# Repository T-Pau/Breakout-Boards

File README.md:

# Connector Breakout Boards

### Easy Access to Pins of Common Connectors for Prototyping or Testing

## What Are These Boards?

They provide easy access to each pin of a connector via a pin header, labeled with the pin number and its use. If a connector contains multiple ground pins, these can be connected on the board via jumpers.

## Why Use These Boards?

They make testing or prototyping cables easier by providing a robust connection and avoiding mixing up pins.

## Getting Started

You can produce these boards

## D-Sub 9, 15, and 25

These connectors saw a wide variety of uses, therefore only pin numbers are provided on the silk screen. Each breakout board contains a pins and a socket connector.

### D-Sub 9 Bill of Materials

Amount | Part 
-------|-----
1      | 90° D-Sub-9 pins
1      | 90° D-Sub-9 socket
1      | 2x5 pin header

### D-Sub 15 Bill of Materials

Amount | Part 
-------|-----
1      | 90° D-Sub-15 pins
1      | 90° D-Sub-15 socket
1      | 2x8 pin header

### D-Sub 25 Bill of Materials

Amount | Part 
-------|-----
1      | 90° D-Sub-25 plug
1      | 90° D-Sub-25 socket
1      | 2x13 pin header

## VGA Breakout Board

This board exposes each pin of a VGA connector on a pin header. It also allows connecting each of the GND pins via jumpers.

### Bill of Materials

Amount | Part 
-------|-----
1      | 90° D-Sub-15 HD socket
1      | 2x4 pin header
1      | 2x8 pin header
4      | jumper

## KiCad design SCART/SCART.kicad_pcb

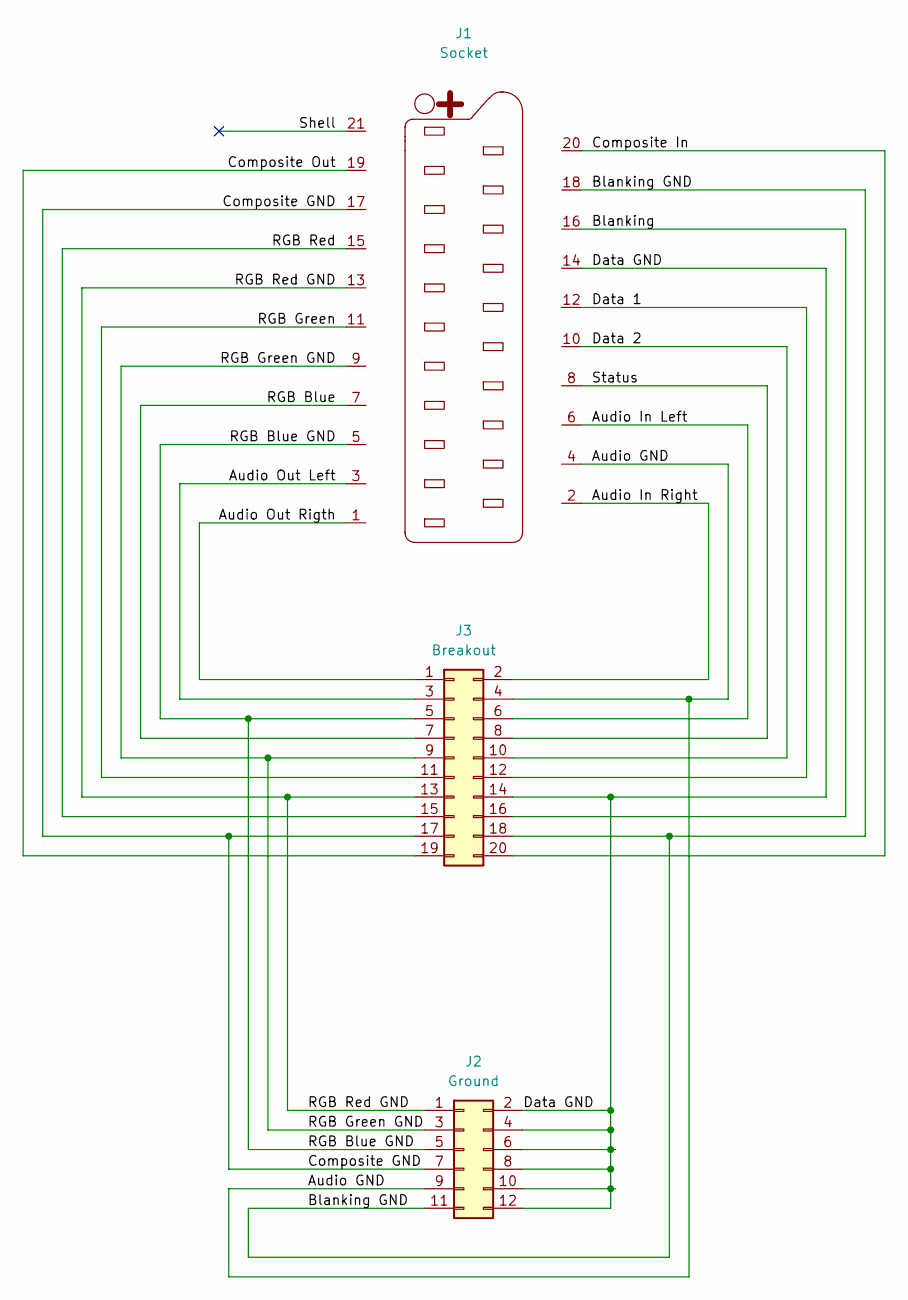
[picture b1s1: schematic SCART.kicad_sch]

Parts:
J1: Socket; SCART
J2: Ground; PinSocket_2x06_P2.54mm_Vertical
J3: Breakout; PinSocket_2x10_P2.54mm_Vertical

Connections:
/Audio GND: J1.4, J2.9, J3.4
/Audio In Left: J1.6, J3.6
/Audio In Right: J1.2, J3.2
/Audio Out Left: J1.3, J3.3
/Audio Out Rigth: J1.1, J3.1
/Blanking: J1.16, J3.16
/Blanking GND: J1.18, J2.11, J3.18
/Composite GND: J1.17, J2.7, J3.17
/Composite In: J1.20, J3.20
/Composite Out: J1.19, J3.19
/Data 1: J1.12, J3.12
/Data 2: J1.10, J3.10
/Data GND: J1.14, J2.2, J2.4, J2.6, J2.8, J2.10, J2.12, J3.14
/RGB Blue: J1.7, J3.7
/RGB Blue GND: J1.5, J2.5, J3.5
/RGB Green: J1.11, J3.11
/RGB Green GND: J1.9, J2.3, J3.9
/RGB Red: J1.15, J3.15
/RGB Red GND: J1.13, J2.1, J3.13
/Shell: J1.21
/Status: J1.8, J3.8

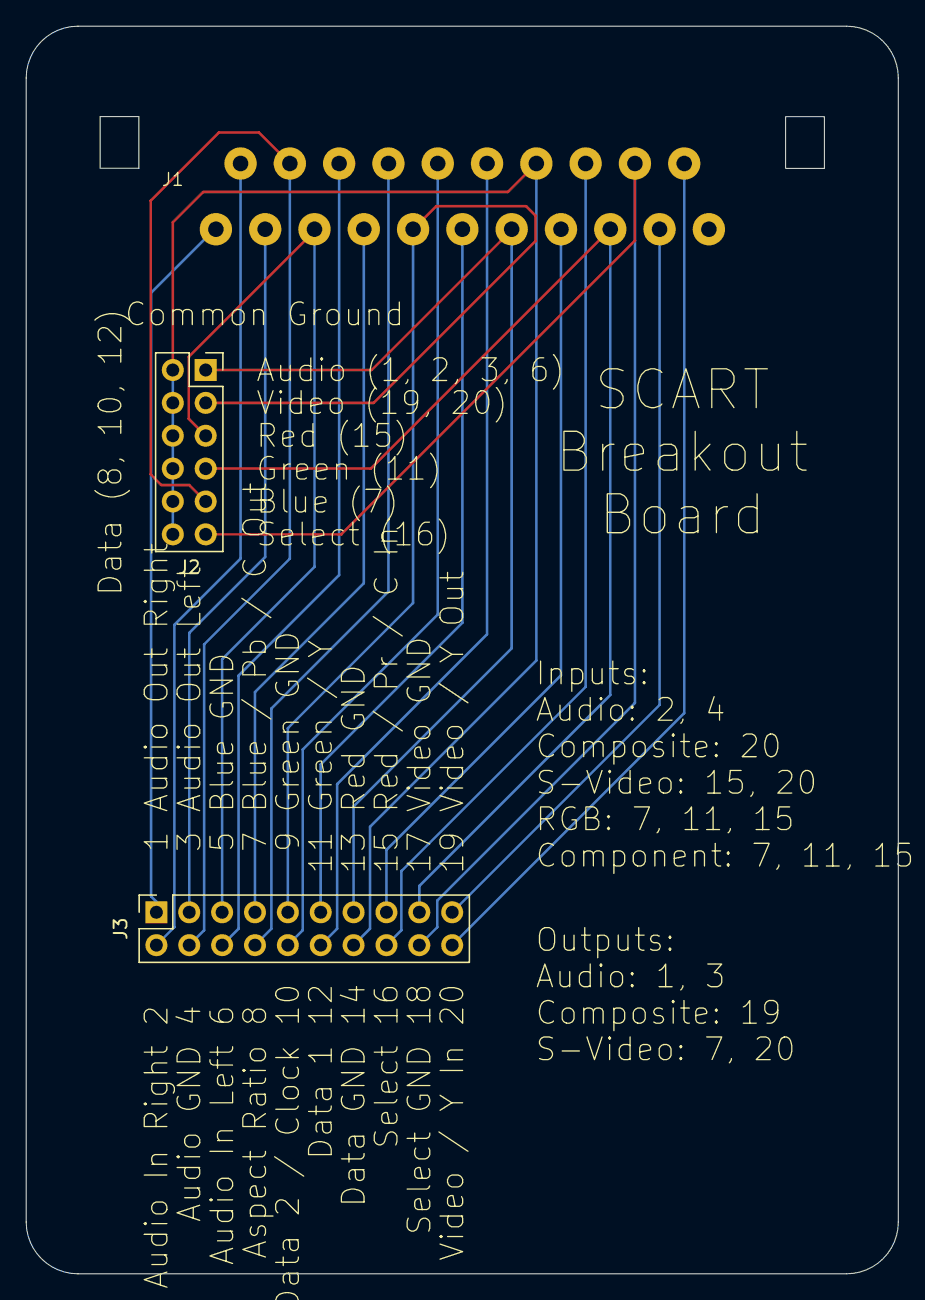
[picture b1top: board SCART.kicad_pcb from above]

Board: 2 copper layers, 67.4 x 96.4 mm, 3 parts (0 on the bottom side), 20 nets.

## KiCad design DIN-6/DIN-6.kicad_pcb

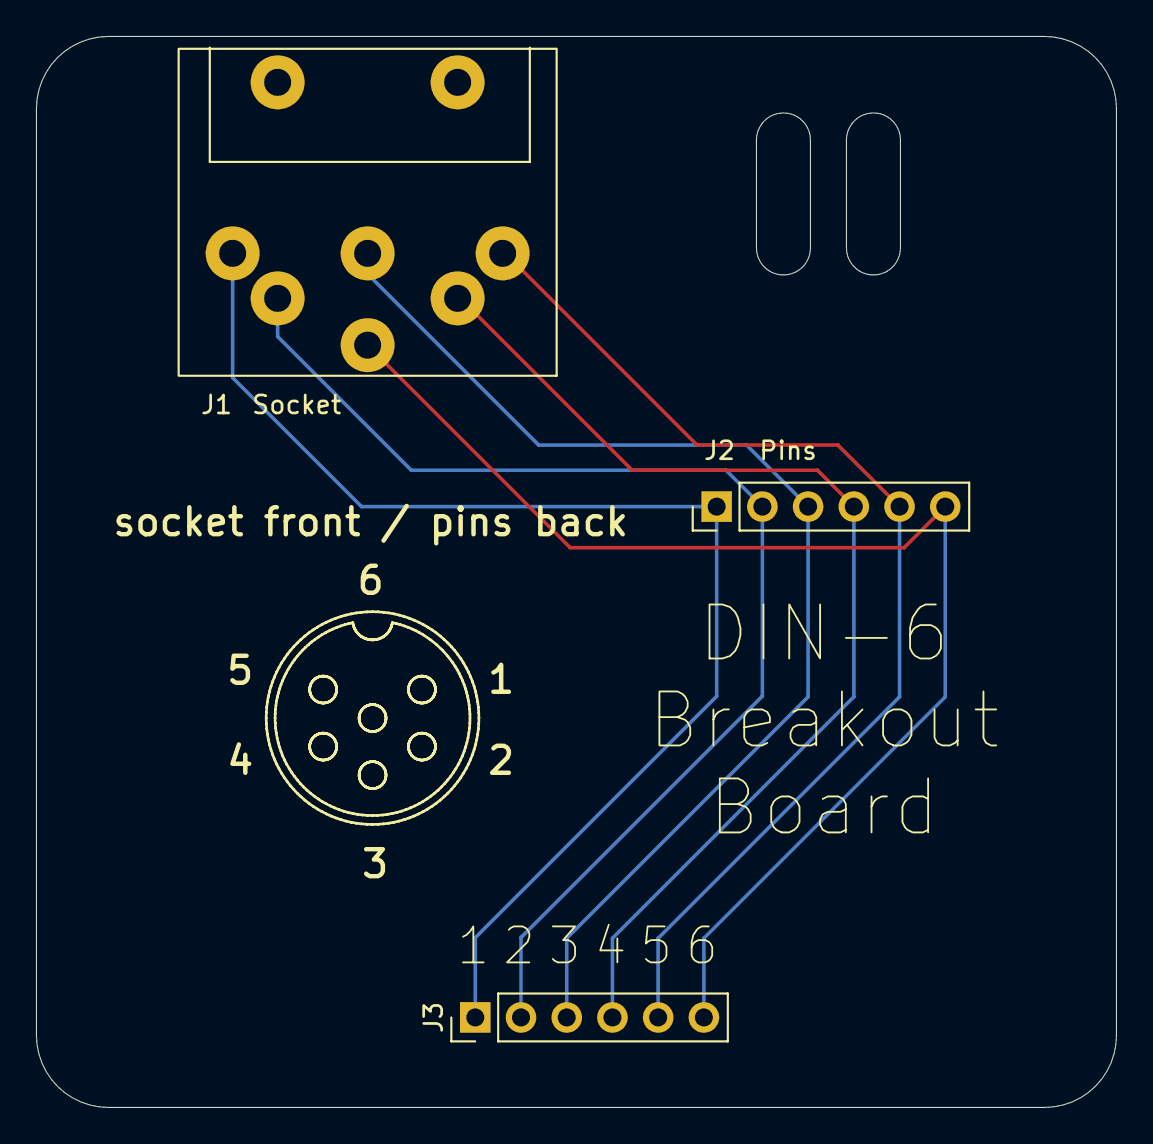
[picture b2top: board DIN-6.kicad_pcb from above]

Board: 2 copper layers, 60.0 x 59.5 mm, 3 parts (0 on the bottom side), 6 nets.

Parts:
J1: Socket; DIN-6
J2: Pins; PinHeader_1x06_P2.54mm_Vertical
J3: Breakout; PinHeader_1x06_P2.54mm_Vertical

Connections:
unnamed: J1.1, J2.1, J3.1
unnamed: J1.2, J2.2, J3.2
unnamed: J1.3, J2.3, J3.3
unnamed: J1.4, J2.4, J3.4
unnamed: J1.5, J2.5, J3.5
unnamed: J1.6, J2.6, J3.6

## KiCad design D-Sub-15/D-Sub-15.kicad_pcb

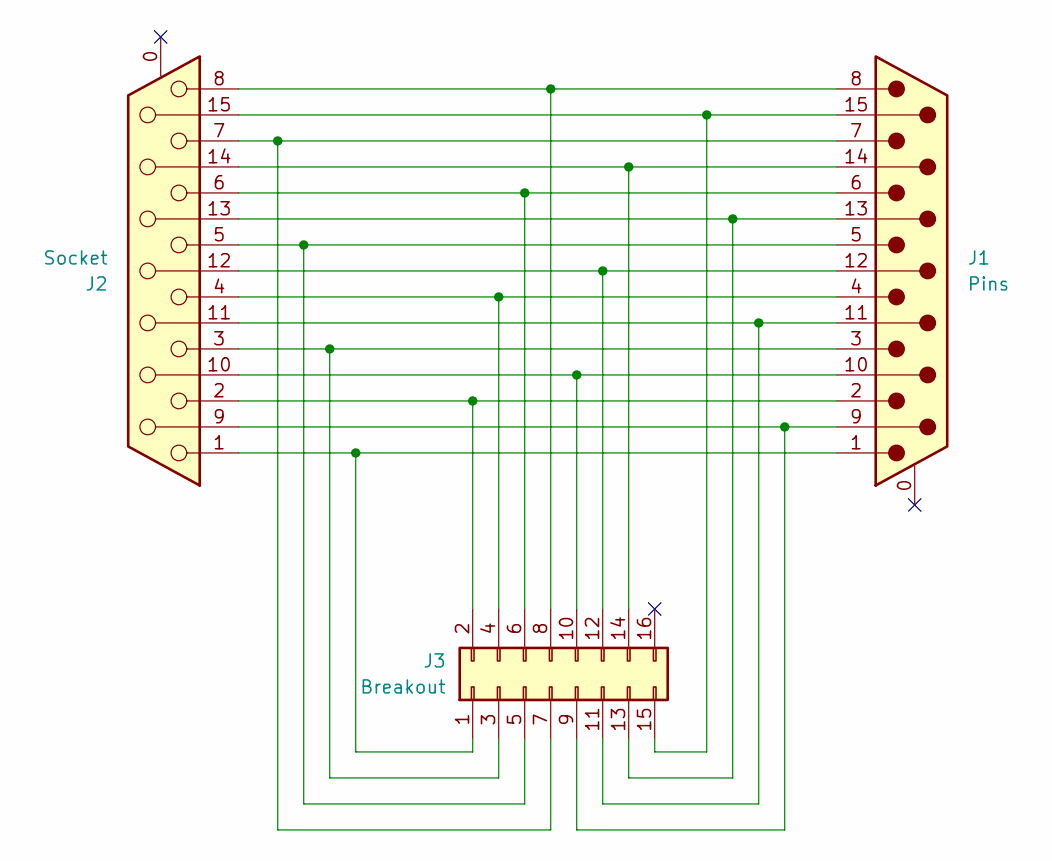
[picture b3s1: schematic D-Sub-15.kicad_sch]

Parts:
J1: Pins; DSUB-15_Pins_Horizontal_P2.77x2.84mm_EdgePinOffset7.70mm_Ho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
J2: Socket; DSUB-15_Socket_Horizontal_P2.77x2.84mm_EdgePinOffset7.70mm_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
J3: Breakout; PinHeader_2x08_P2.54mm_Vertical

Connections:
unnamed: J1.9, J2.9, J3.9
unnamed: J1.10, J2.10, J3.10
unnamed: J1.12, J2.12, J3.12
unnamed: J1.13, J2.13, J3.13
unnamed: J1.14, J2.14, J3.14
unnamed: J1.15, J2.15, J3.15
unnamed: J1.11 (P111), J2.11 (P111), J3.11
unnamed: J1.1, J2.1, J3.1
unnamed: J1.2, J2.2, J3.2
unnamed: J1.3, J2.3, J3.3
unnamed: J1.4, J2.4, J3.4
unnamed: J1.5, J2.5, J3.5
unnamed: J1.6, J2.6, J3.6
unnamed: J1.7, J2.7, J3.7
unnamed: J1.8, J2.8, J3.8

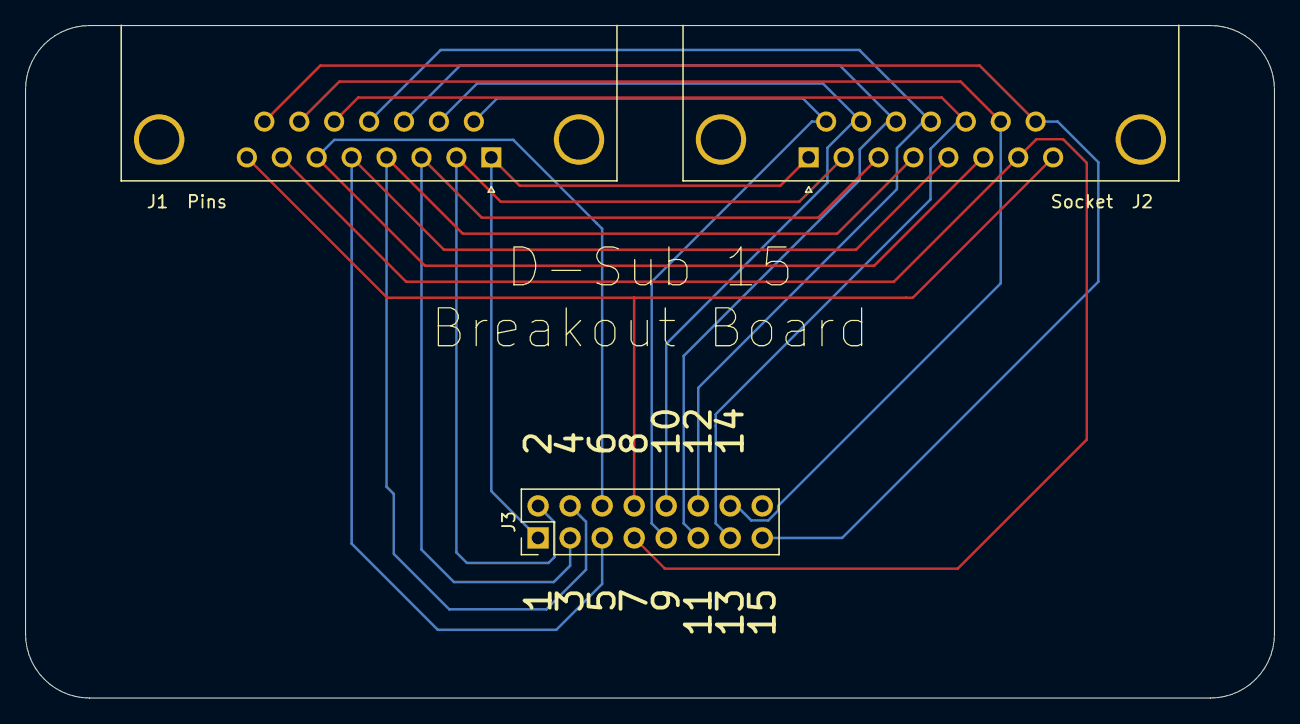
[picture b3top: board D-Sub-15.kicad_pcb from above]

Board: 2 copper layers, 99.1 x 53.3 mm, 3 parts (0 on the bottom side), 15 nets.

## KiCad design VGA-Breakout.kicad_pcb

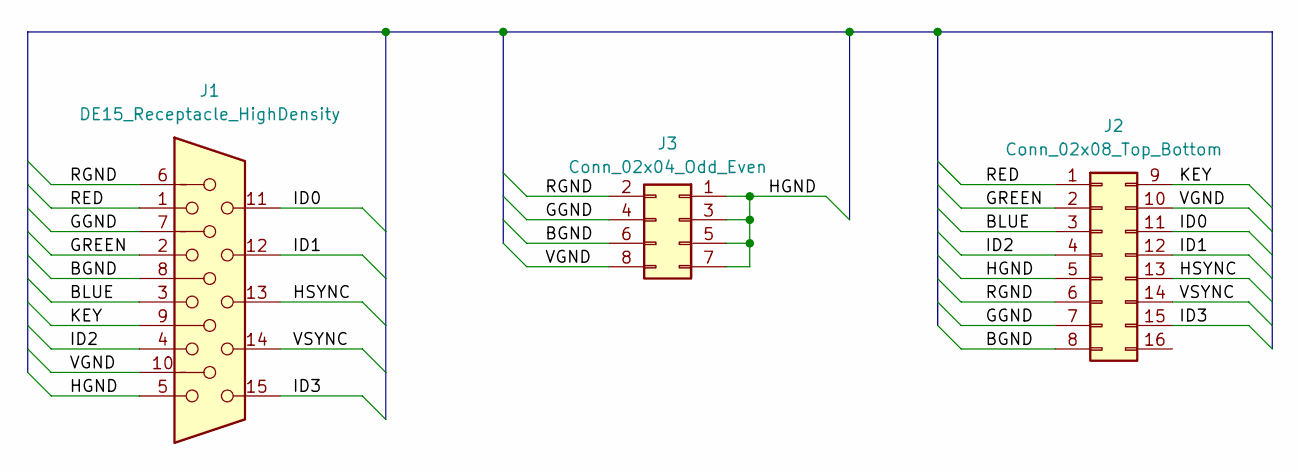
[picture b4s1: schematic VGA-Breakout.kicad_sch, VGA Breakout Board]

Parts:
J1: DE15_Receptacle_HighDensity; DSUB-15-HD_Female_Horizontal_P2.29x1.98mm_EdgePinOffset8.35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
J2: Conn_02x08_Top_Bottom; PinHeader_2x08_P2.54mm_Vertical
J3: Conn_02x04_Odd_Even; PinHeader_2x04_P2.54mm_Vertical

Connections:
/BGND: J1.8, J2.8, J3.6
/BLUE: J1.3, J2.3
/GGND: J1.7, J2.7, J3.4
/GREEN: J1.2, J2.2
/HGND: J1.5, J2.5, J3.1, J3.3, J3.5, J3.7
/HSYNC: J1.13, J2.13
/ID0: J1.11, J2.11
/ID1: J1.12, J2.12
/ID2: J1.4, J2.4
/ID3: J1.15, J2.15
/KEY: J1.9, J2.9
/RED: J1.1, J2.1
/RGND: J1.6, J2.6, J3.2
/VGND: J1.10, J2.10, J3.8
/VSYNC: J1.14, J2.14

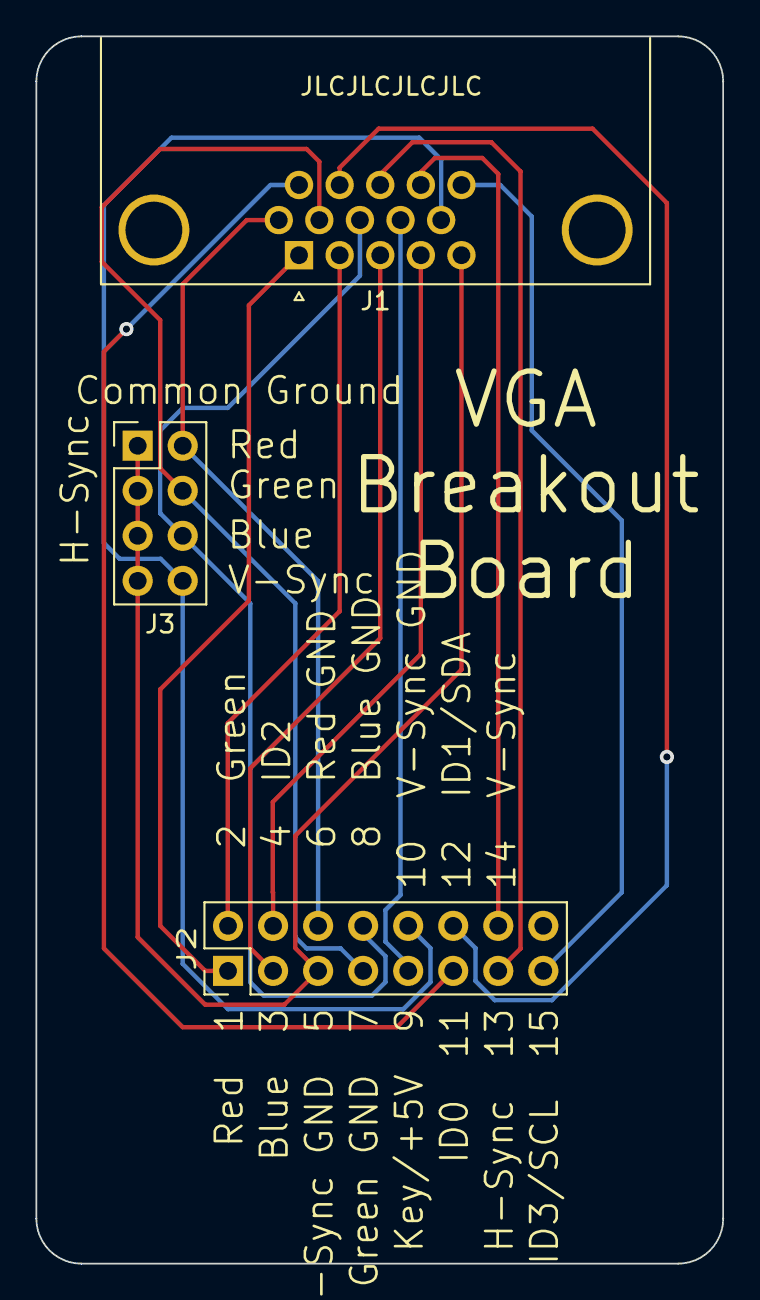
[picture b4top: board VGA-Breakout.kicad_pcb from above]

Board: 2 copper layers, 38.7 x 69.2 mm, 3 parts (0 on the bottom side), 15 nets.

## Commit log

2024-09-28 Initial commit.
2024-09-28 Add README.
2024-11-09 Update PCB layout.
2024-11-09 Move to correct directory, update files.
2025-05-30 Move one directory up.
2025-06-02 Add more breakout boards.
2025-06-02 Corerect URL.
2025-06-03 Improve layouts, add DIN-8 270° board.
2025-06-03 Begin SCART breakout board.
2025-06-09 Finish SCART board.
2025-06-11 Adapt to fixed footprint.

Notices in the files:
D-Sub-15/D-Sub-15.kicad_pcb:
©2025 Dieter Baron
VGA-Breakout.kicad_pcb:
©2024 Dieter Baron
